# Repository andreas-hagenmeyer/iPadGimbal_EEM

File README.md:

# iPad Gimbal - Energieeffiziente Mikrocontroller

Git repo für die Verwaltung des Schaltplans und des PCB layouts.

Schaltplan erstellt mittels KiCad

## ToDo:

- [x] Review Schaltplan
- [x] Review PCB Layout
- [x] Bestellung Komponenten
- [x] Bestellung PCB 
- [x] Löten der PCB
- [x] Inbetriebnahme
  
Projekt wurde im WS 22/23 abgeschossen. Die Enddokumentation des Projektes befindet sich im Teams-Kanal der Vorlesung

## 3D Ansicht PCB

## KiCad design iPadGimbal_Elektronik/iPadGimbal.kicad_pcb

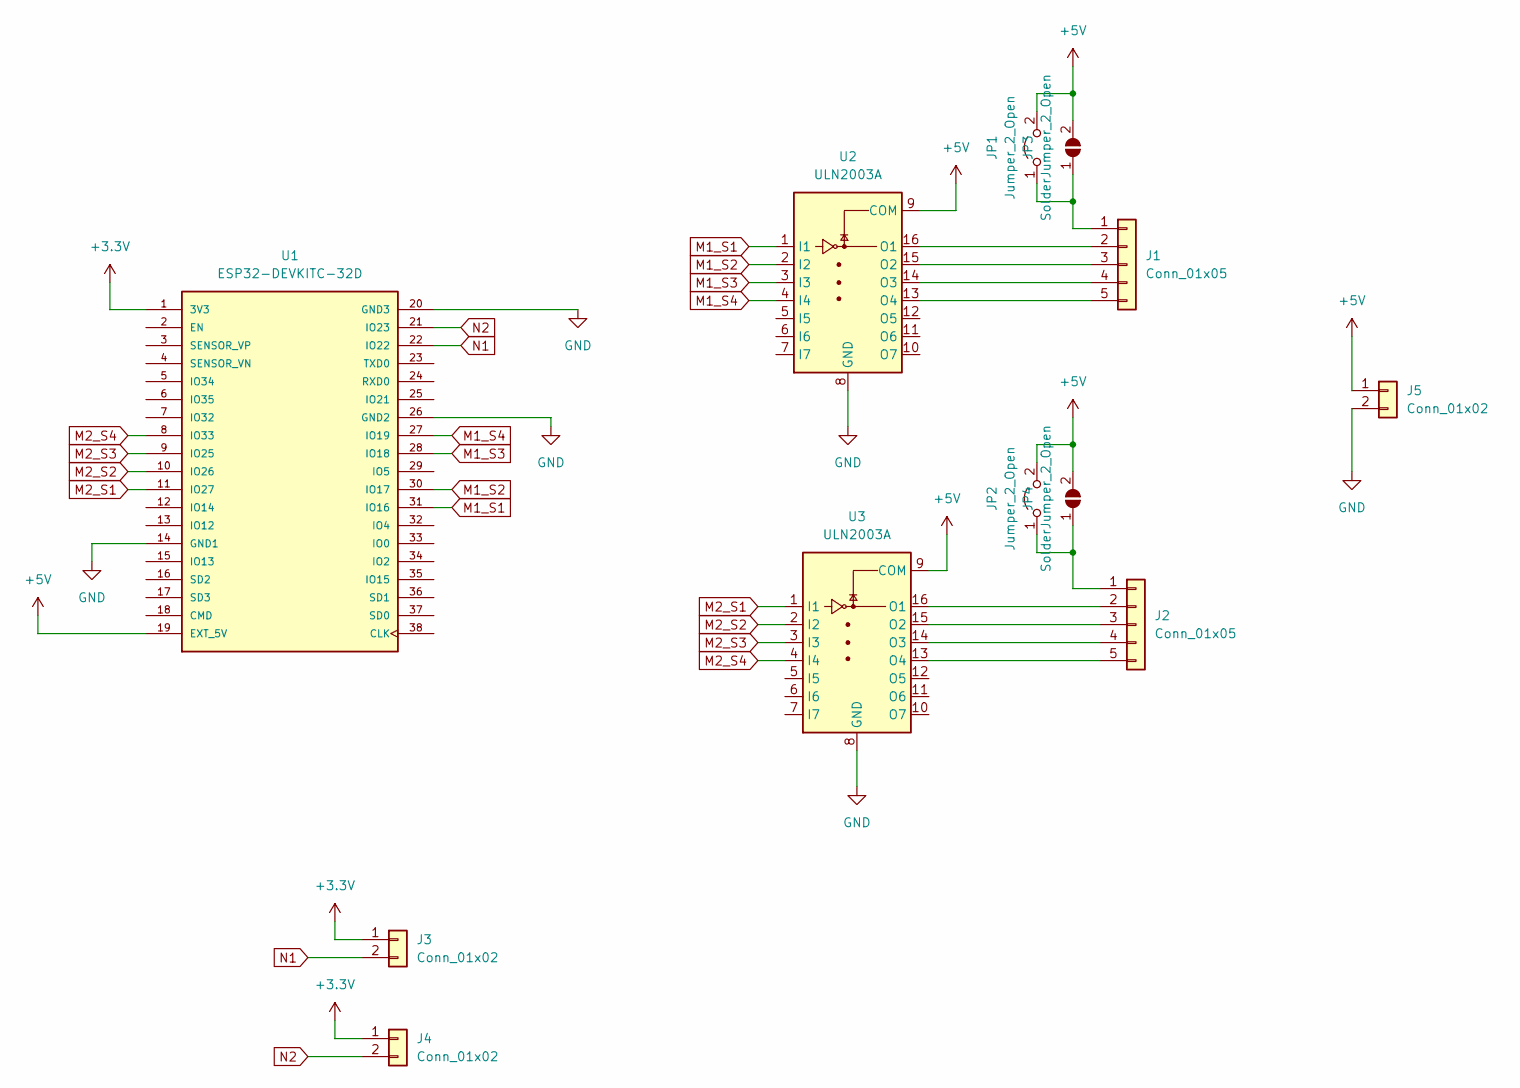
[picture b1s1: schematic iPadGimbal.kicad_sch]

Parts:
J1, J2: Conn_01x05; JST_XH_B5B-XH-AM_1x05_P2.50mm_Vertical
J3, J4: Conn_01x02; JST_XH_B2B-XH-AM_1x02_P2.50mm_Vertical
J5: Conn_01x02; PinHeader_1x02_P2.54mm_Vertical
JP1, JP2: Jumper_2_Open; PinHeader_1x02_P2.54mm_Vertical
JP3, JP4: SolderJumper_2_Open; SolderJumper-2_P1.3mm_Open_RoundedPad1.0x1.5mm
U1: ESP32-DEVKITC-32D; MODULE_ESP32-DEVKITC-32D_TWO-ROW; PARTREV 4
U2, U3: ULN2003A; SOIC-16_3.9x9.9mm_P1.27mm

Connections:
+3.3V: J3.1, J4.1, U1.1 (3V3)
+5V: J5.1, JP1.2 (B), JP2.2 (B), JP3.2 (B), JP4.2 (B), U1.19 (EXT_5V), U2.9 (COM), U3.9 (COM)
GND: J5.2, U1.14 (GND1), U1.20 (GND3), U1.26 (GND2), U2.8 (GND), U3.8 (GND)
M1_S1: U1.31 (IO16), U2.1 (I1)
M1_S2: U1.30 (IO17), U2.2 (I2)
M1_S3: U1.28 (IO18), U2.3 (I3)
M1_S4: U1.27 (IO19), U2.4 (I4)
M2_S1: U1.11 (IO27), U3.1 (I1)
M2_S2: U1.10 (IO26), U3.2 (I2)
M2_S3: U1.9 (IO25), U3.3 (I3)
M2_S4: U1.8 (IO33), U3.4 (I4)
N1: J3.2, U1.22 (IO22)
N2: J4.2, U1.21 (IO23)
unnamed: J1.1, JP1.1 (A), JP3.1 (A)
unnamed: J1.2, U2.16 (O1)
unnamed: J1.3, U2.15 (O2)
unnamed: J1.4, U2.14 (O3)
unnamed: J1.5, U2.13 (O4)
unnamed: J2.1, JP2.1 (A), JP4.1 (A)
unnamed: J2.2, U3.16 (O1)
unnamed: J2.3, U3.15 (O2)
unnamed: J2.4, U3.14 (O3)
unnamed: J2.5, U3.13 (O4)

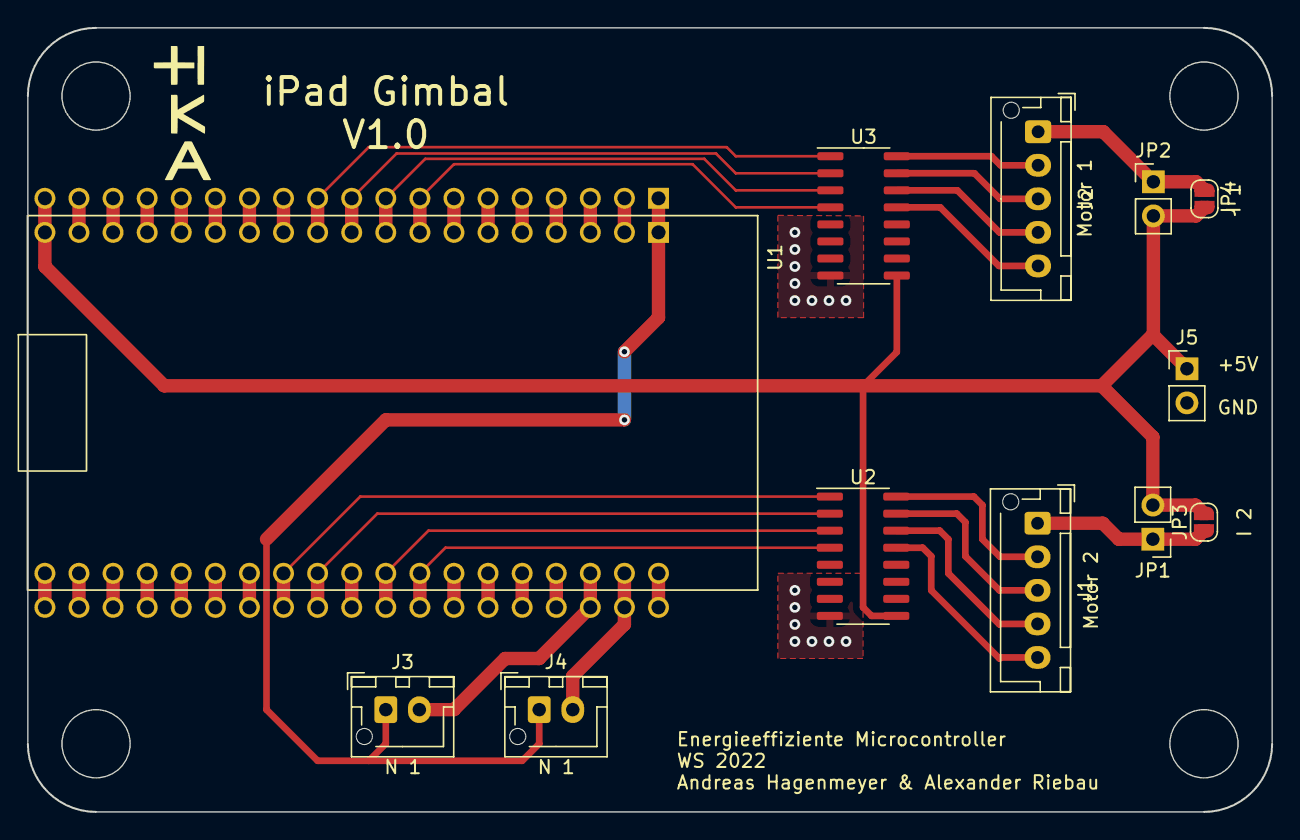
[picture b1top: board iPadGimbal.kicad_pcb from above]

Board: 2 copper layers, 92.7 x 58.4 mm, 12 parts (0 on the bottom side), 23 nets.

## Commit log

2022-11-02 added KiCad files
2022-11-02 add Schematic pdf
2022-11-02 Markdown geschrieben
2022-11-09 Silkscreen angepasst
2022-11-09 Silkscreen Namen hinzugefügt
2022-11-09 Bild aktualisiert
2022-11-22 Bennenung im Schaltplan korregiert; MassePin des ESP's korregiert
2022-11-22 PDF aktualisiert
